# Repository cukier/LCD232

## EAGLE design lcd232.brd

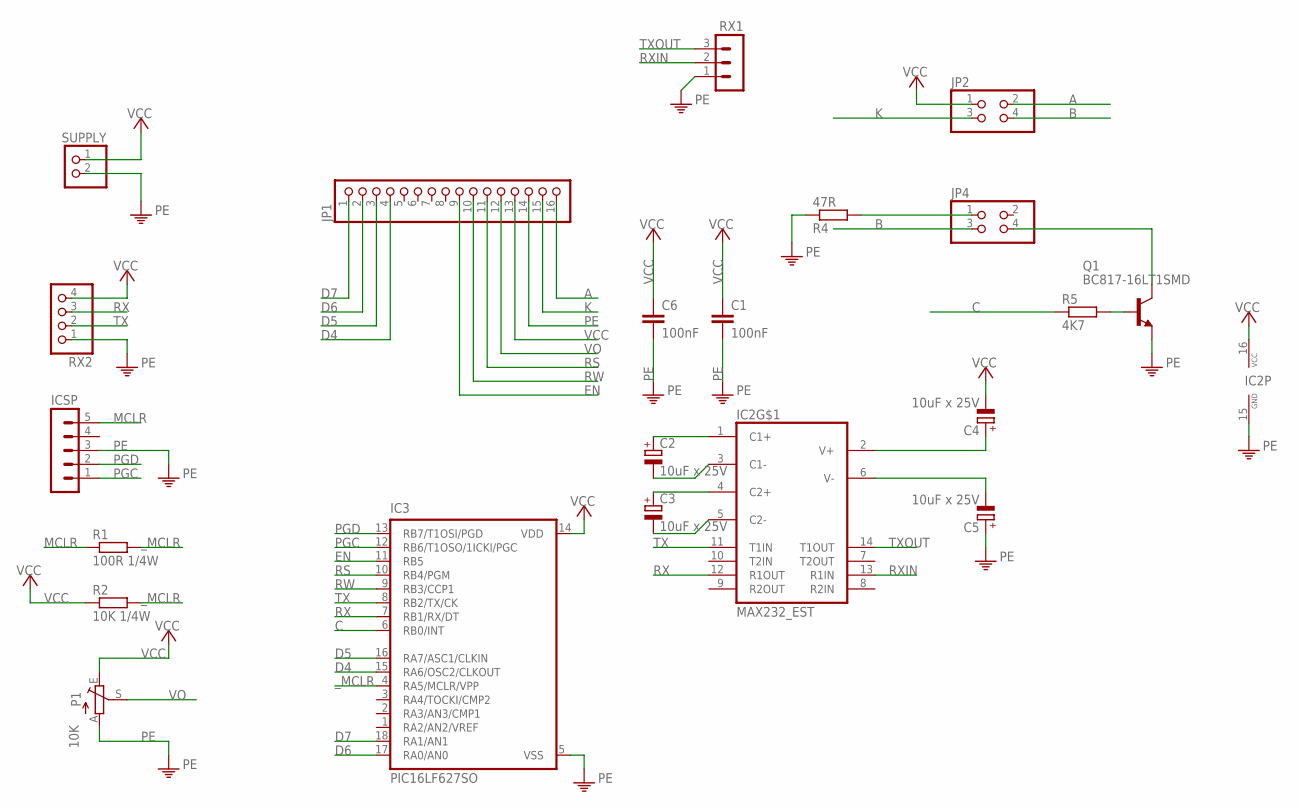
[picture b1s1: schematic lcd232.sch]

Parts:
C1, C6: 100nF; C0805
C2, C3, C4, C5: 10uF x 25V; E2-4
IC2: MAX232_EST; SO16_EST
IC3: PIC16LF627SO; SO-18W
ICSP: MA05-1
JP1: PINHD-1X16; 1X16
JP2, JP4: PINHD-2X2; 2X02
P1: 10K; CA9V
Q1: BC817-16LT1SMD; SOT23-BEC
R1: 100R 1/4W; M0805
R2: 10K 1/4W; M0805
R4: 47R; M0805
R5: 4K7; M0805
RX1: MA03-1
RX2: PINHD-1X4; 1X04
SUPPLY: PINHD-1X2; 1X02

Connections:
A: JP1.16, JP2.2
B: JP2.4, JP4.3
C: IC3.6 (RB0/INT), R5.1
D4: IC3.15 (RA6/OSC2/CLKOUT), JP1.4
D5: IC3.16 (RA7/ASC1/CLKIN), JP1.3
D6: IC3.17 (RA0/AN0), JP1.2
D7: IC3.18 (RA1/AN1), JP1.1
EN: IC3.11 (RB5), JP1.9
K: JP1.15, JP2.3
MCLR: ICSP.5, R1.1
unnamed: C3.+, IC2.4 (C2+)
unnamed: C3.-, IC2.5 (C2-)
unnamed: Q1.B, R5.2
unnamed: C2.+, IC2.1 (C1+)
unnamed: C2.-, IC2.3 (C1-)
unnamed: C4.+, IC2.2 (V+)
unnamed: JP4.4, Q1.C
unnamed: C5.-, IC2.6 (V-)
unnamed: JP4.1, R4.2
PE: C1.2, C5.+, C6.2, IC2.15 (GND), IC3.5 (VSS), ICSP.3, JP1.14, P1.A, Q1.E, R4.1, RX1.1, RX2.1, SUPPLY.2
PGC: IC3.12 (RB6/T1OSO/1ICKI/PGC), ICSP.1
PGD: IC3.13 (RB7/T1OSI/PGD), ICSP.2
RS: IC3.10 (RB4/PGM), JP1.11
RW: IC3.9 (RB3/CCP1), JP1.10
RX: IC2.12 (R1OUT), IC3.7 (RB1/RX/DT), RX2.3
RXIN: IC2.13 (R1IN), RX1.2
TX: IC2.11 (T1IN), IC3.8 (RB2/TX/CK), RX2.2
TXOUT: IC2.14 (T1OUT), RX1.3
VCC: C1.1, C4.-, C6.1, IC2.16 (VCC), IC3.14 (VDD), JP1.13, JP2.1, P1.E, R2.1, RX2.4, SUPPLY.1
VO: JP1.12, P1.S
_MCLR: IC3.4 (RA5/MCLR/VPP), R1.2, R2.2

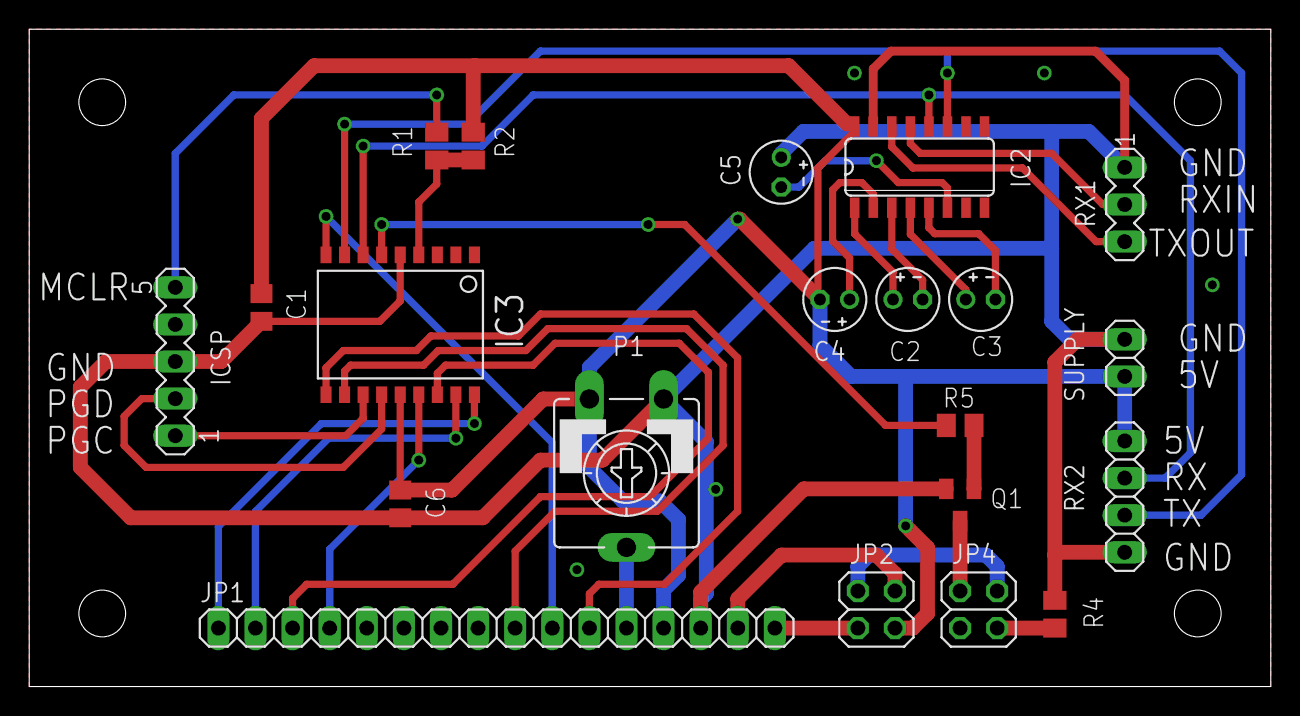
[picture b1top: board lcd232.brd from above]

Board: 2 copper layers, 85.0 x 45.0 mm, 21 parts (0 on the bottom side), 31 nets.

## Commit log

2013-04-19 V1.0
2013-04-22 funcionando \r, \n, e \f
2013-04-22 voltando estado anterior
2013-06-21 adicionadas desenhos das placas prontas
2013-07-19 corrigido bug da string muito grande
2013-07-19 bugs de string e tempo concertadas
2013-09-06 alteracão feita para RW do lcd, agora ligada ao pino B3
2013-10-03 aumento tempo espera
2014-02-04 gravado 4 fev 2014
2014-02-19 bugs
2014-02-25 resolvido problema de estouro de buffer
2014-02-26 alterado pino rs para A2 (antes B4) e en para A3 (antes B5)
2014-08-12 backup
2014-09-12 buffer maior
2014-10-07 uc nao dorme mais
2014-10-08 ultimo commit
2015-02-26 melhorias de codigo, sincronizado de trena_interruption
2015-02-26 sem interrucao
2015-02-27 usando caractere de controle '\r'
2015-02-27 sem "done"
2015-08-04 linux config
